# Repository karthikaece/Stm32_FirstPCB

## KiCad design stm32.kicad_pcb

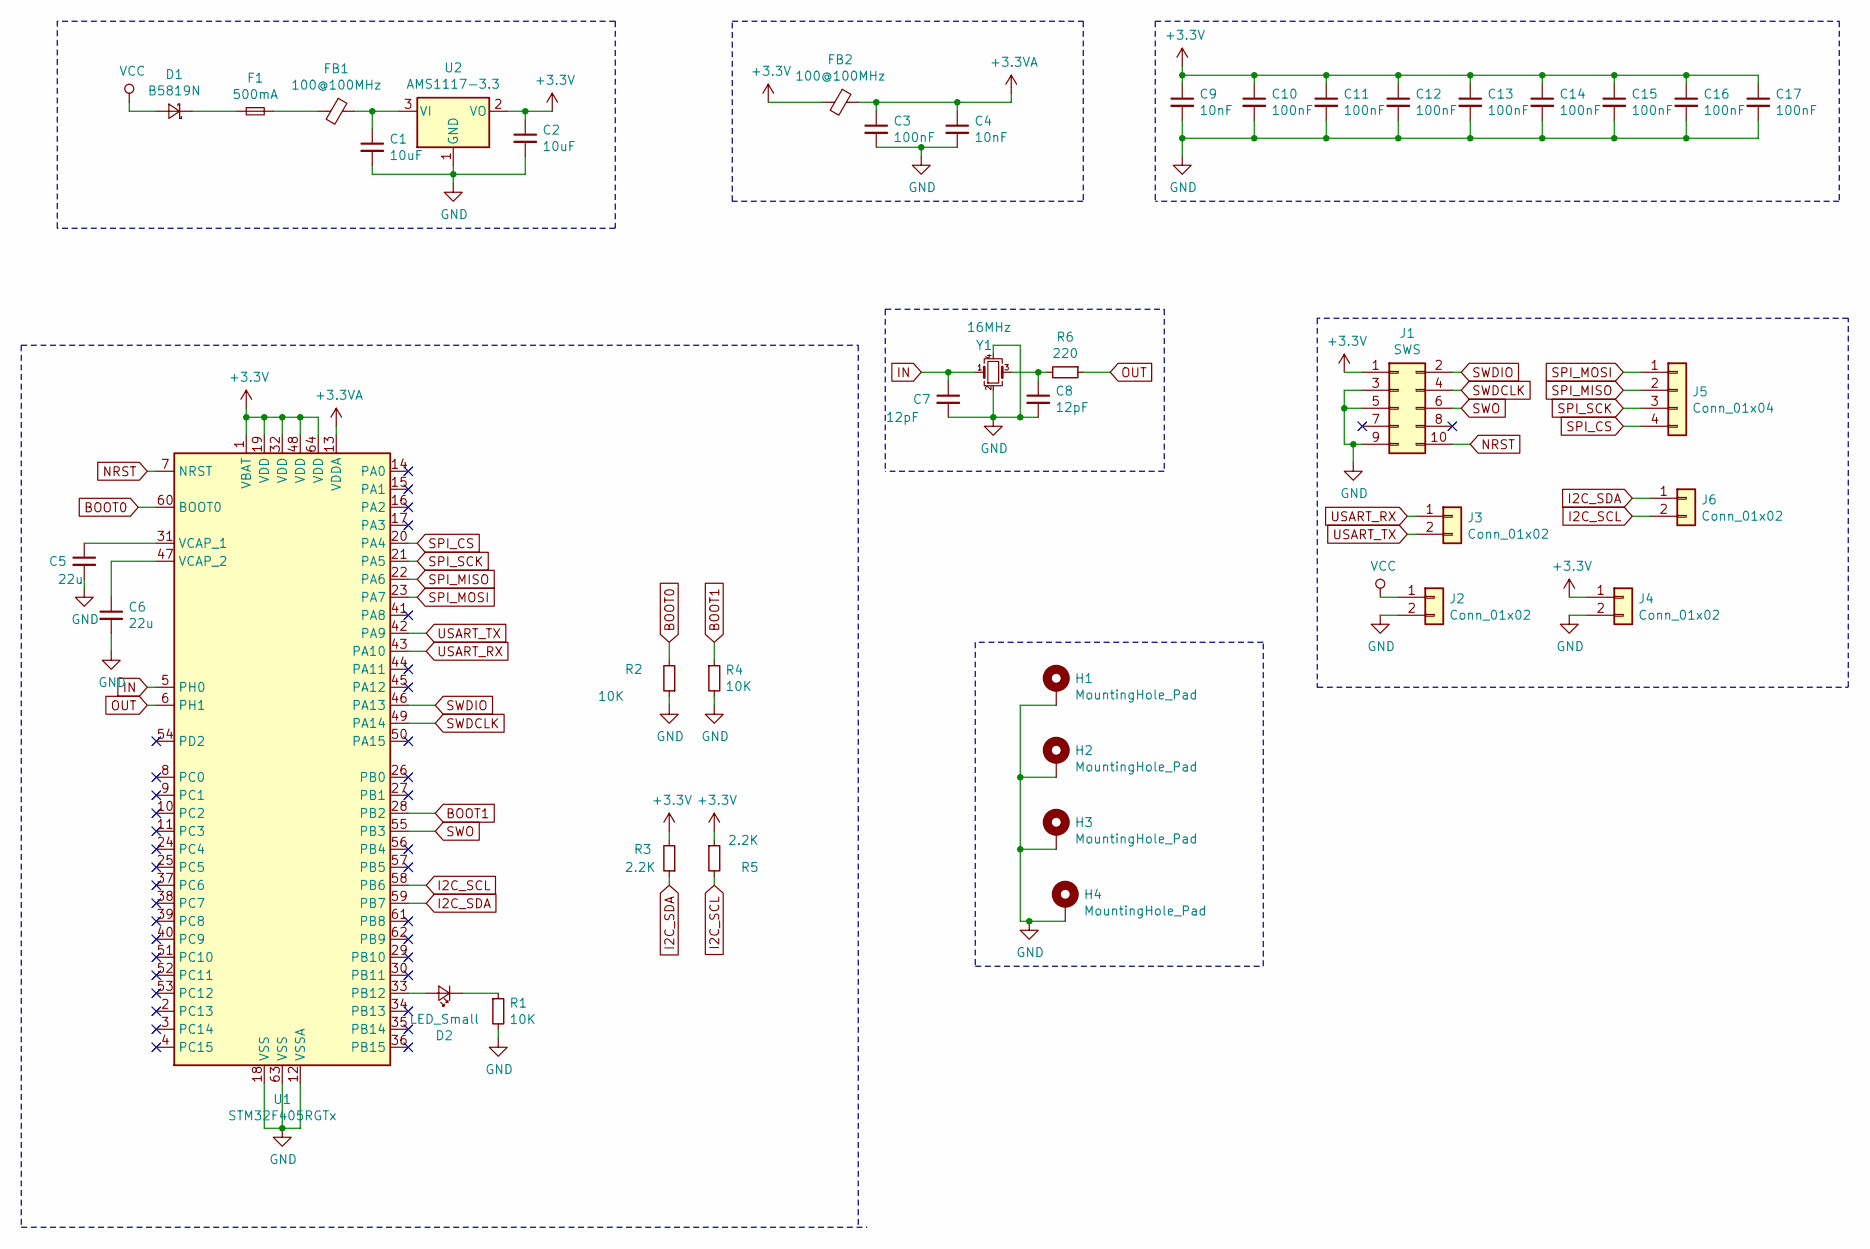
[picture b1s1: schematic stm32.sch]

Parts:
C1, C2: 10uF
C3, C10, C11, C12, C13, C14, C15, C16, C17: 100nF
C4, C9: 10nF
C5, C6: 22u
C7, C8: 12pF
D1: B5819N
D2: LED_Small
F1: 500mA
FB1, FB2: 100@100MHz
H1, H2, H3, H4: MountingHole_Pad
J1: SWS
J2, J3, J4, J6: Conn_01x02
J5: Conn_01x04
R1, R2, R4: 10K
R3, R5: 2.2K
R6: 220
U1: STM32F405RGTx; LQFP-64_10x10mm_P0.5mm
U2: AMS1117-3.3; SOT-223-3_TabPin2
Y1: 16MHz

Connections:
+3.3VA: C3.1, C4.1, FB2.1, U1.13 (VDDA)
+3V3: C2.1, C9.1, C10.1, C11.1, C12.1, C13.1, C14.1, C15.1, C16.1, C17.1, FB2.2, J1.1, J4.1, R3.2, R5.1, U1.1 (VBAT), U1.19 (VDD), U1.32 (VDD), U1.48 (VDD), U1.64 (VDD), U2.2 (VO)
BOOT0: R2.2, U1.60 (BOOT0)
BOOT1: R4.1, U1.28 (PB2)
GND: C1.2, C2.2, C3.2, C4.2, C5.2, C6.2, C7.2, C8.2, C9.2, C10.2, C11.2, C12.2, C13.2, C14.2, C15.2, C16.2, C17.2, H1.1, H2.1, H3.1, H4.1, J1.3, J1.5, J1.9, J2.2, J4.2, R1.2, R2.1, R4.2, U1.12 (VSSA), U1.18 (VSS), U1.63 (VSS), U2.1 (GND), Y1.2, Y1.4
I2C_SCL: J6.2, R5.2, U1.58 (PB6)
I2C_SDA: J6.1, R3.1, U1.59 (PB7)
IN: C7.1, U1.5 (PH0), Y1.1
NRST: J1.10, U1.7 (NRST)
unnamed: C1.1, FB1.1, U2.3 (VI)
unnamed: C5.1, U1.31 (VCAP_1)
unnamed: C6.1, U1.47 (VCAP_2)
unnamed: C8.1, R6.2, Y1.3
unnamed: D1.1 (K), F1.1
unnamed: D2.1 (K), R1.1
unnamed: D2.2 (A), U1.33 (PB12)
unnamed: F1.2, FB1.2
OUT: R6.1, U1.6 (PH1)
SPI_CS: J5.4, U1.20 (PA4)
SPI_MISO: J5.2, U1.22 (PA6)
SPI_MOSI: J5.1, U1.23 (PA7)
SPI_SCK: J5.3, U1.21 (PA5)
SWDCLK: J1.4, U1.49 (PA14)
SWDIO: J1.2, U1.46 (PA13)
SWO: J1.6, U1.55 (PB3)
USART_RX: J3.1, U1.43 (PA10)
USART_TX: J3.2, U1.42 (PA9)
VCC: D1.2 (A), J2.1

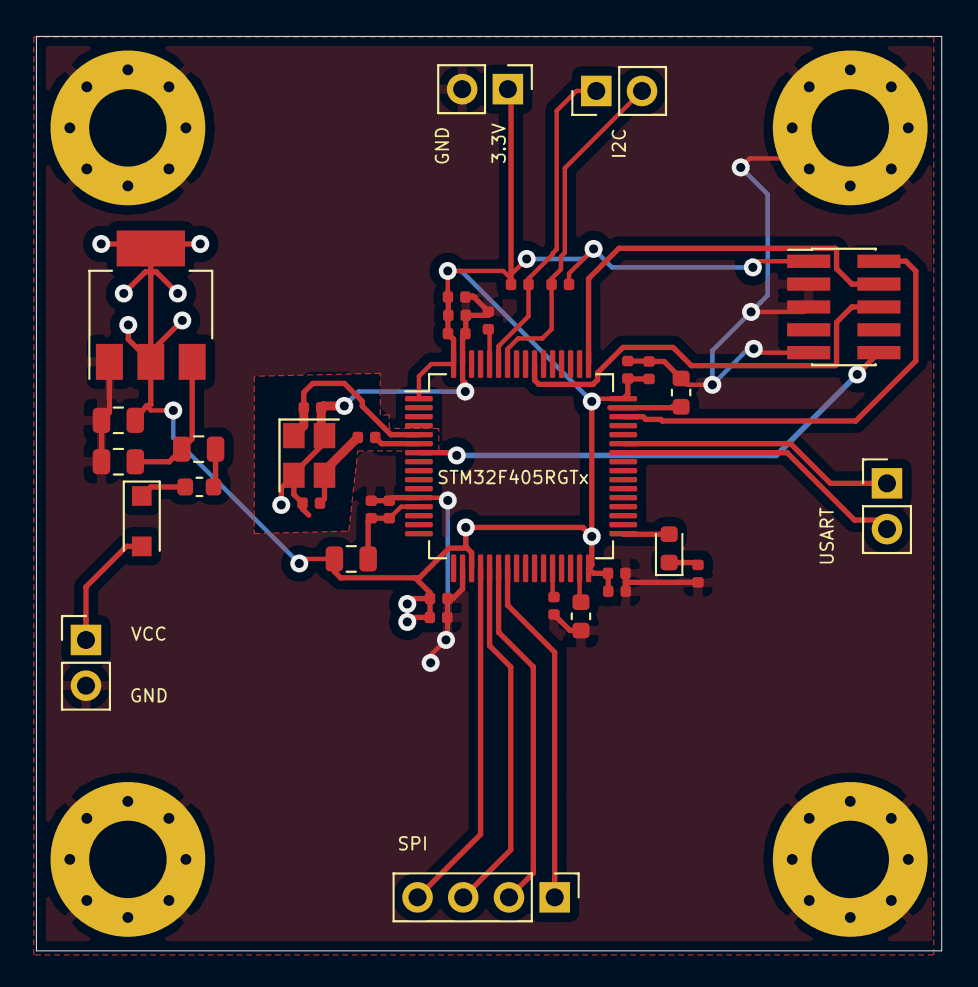
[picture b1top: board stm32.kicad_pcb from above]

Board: 4 copper layers, 50.3 x 50.8 mm, 41 parts (0 on the bottom side), 28 nets.
